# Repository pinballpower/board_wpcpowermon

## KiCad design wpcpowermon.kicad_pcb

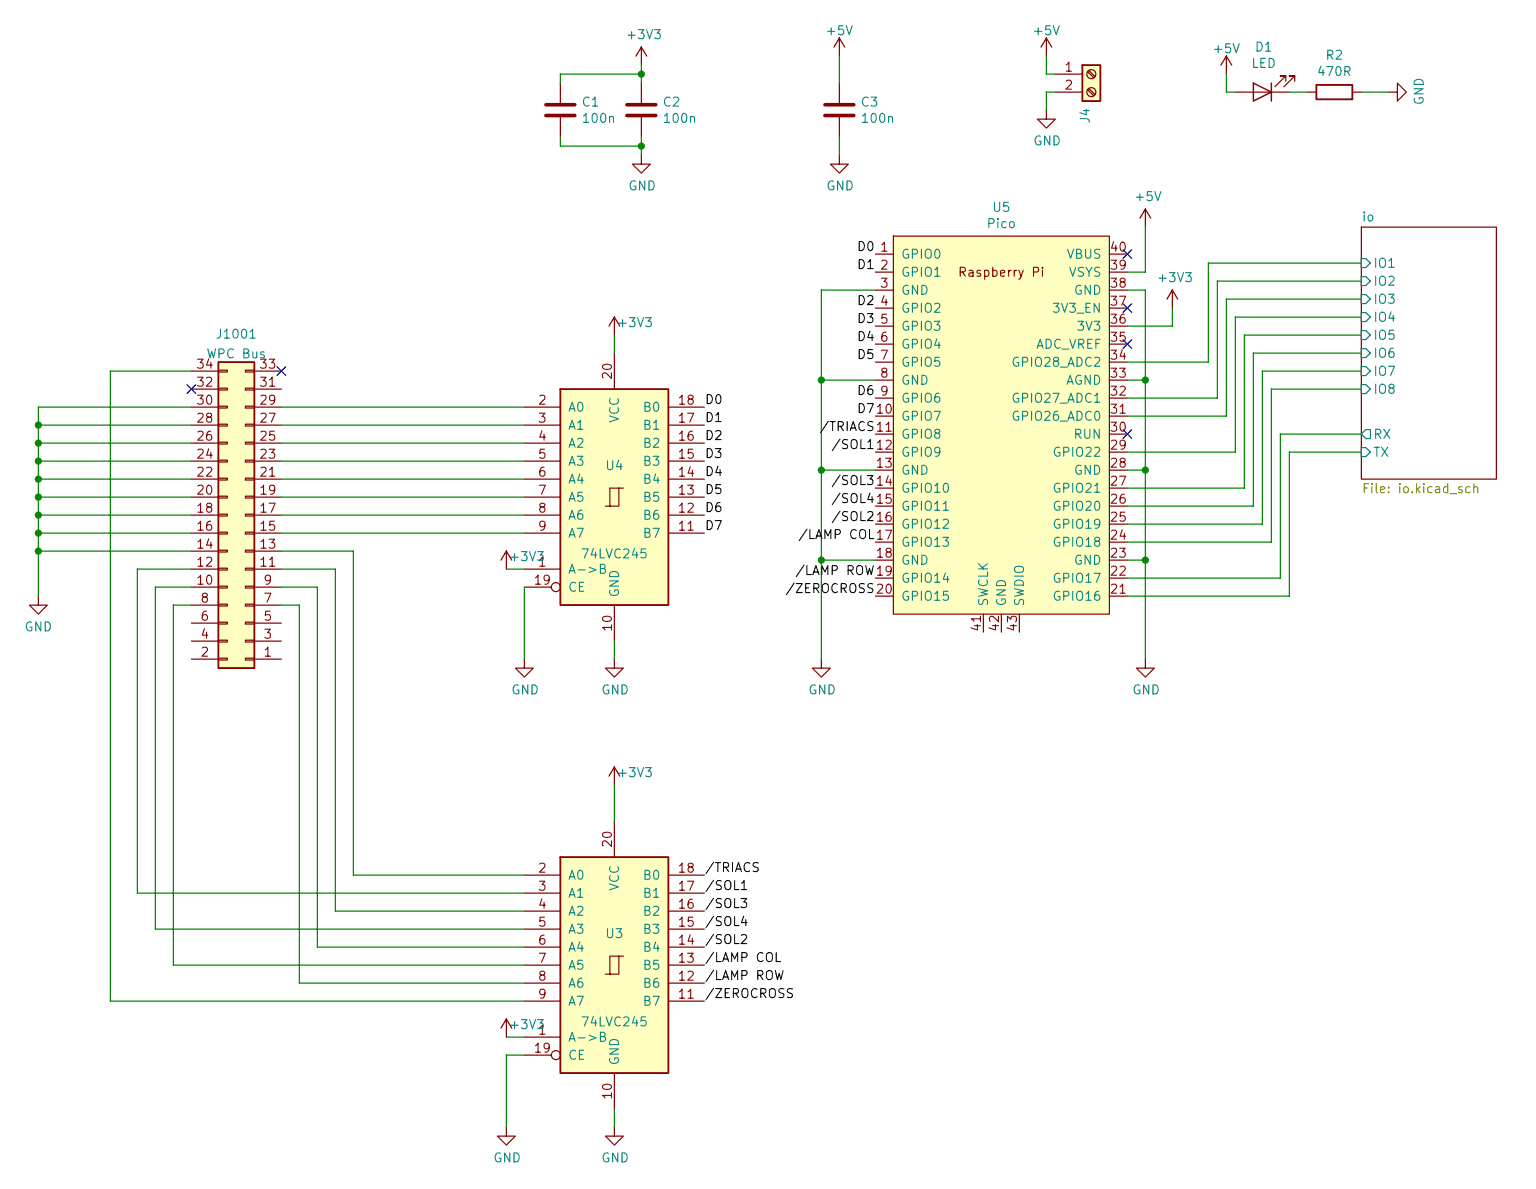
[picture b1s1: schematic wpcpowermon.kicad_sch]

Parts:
C1, C2, C3: 100n; C_Disc_D3.0mm_W2.0mm_P2.50mm
D1: LED; LED_D1.8mm_W3.3mm_H2.4mm
J4: 5V; TerminalBlock_4Ucon_1x02_P3.50mm_Horizontal
J1001: WPC Bus; PinHeader_2x17_P2.54mm_Vertical
R2: 470R; R_Axial_DIN0204_L3.6mm_D1.6mm_P5.08mm_Horizontal
U3, U4: 74LVC245; DIP-20_W7.62mm_LongPads
U5: Pico; RPi_Pico_SMD_TH

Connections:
+3V3: C1.1, C2.1, U3.1 (A->B), U3.20 (VCC), U4.1 (A->B), U4.20 (VCC), U5.36 (3V3)
+5V: C3.1, D1.2 (A), J4.1, U5.39 (VSYS); also elsewhere on the board
/D0: U4.18 (B0), U5.1 (GPIO0)
/D1: U4.17 (B1), U5.2 (GPIO1)
/D2: U4.16 (B2), U5.4 (GPIO2)
/D3: U4.15 (B3), U5.5 (GPIO3)
/D4: U4.14 (B4), U5.6 (GPIO4)
/D5: U4.13 (B5), U5.7 (GPIO5)
/D6: U4.12 (B6), U5.9 (GPIO6)
/D7: U4.11 (B7), U5.10 (GPIO7)
/io/IO1: U5.34 (GPIO28_ADC2); also elsewhere on the board
/io/IO2: U5.32 (GPIO27_ADC1); also elsewhere on the board
/io/IO3: U5.31 (GPIO26_ADC0); also elsewhere on the board
/io/IO4: U5.29 (GPIO22); also elsewhere on the board
/io/IO5: U5.27 (GPIO21); also elsewhere on the board
/io/IO6: U5.26 (GPIO20); also elsewhere on the board
/io/IO7: U5.25 (GPIO19); also elsewhere on the board
/io/IO8: U5.24 (GPIO18); also elsewhere on the board
/io/RX: U5.22 (GPIO17); also elsewhere on the board
/io/TX: U5.21 (GPIO16); also elsewhere on the board
//LAMP COL: U3.13 (B5), U5.17 (GPIO13)
//LAMP ROW: U3.12 (B6), U5.19 (GPIO14)
//SOL1: U3.17 (B1), U5.12 (GPIO9)
//SOL2: U3.14 (B4), U5.16 (GPIO12)
//SOL3: U3.16 (B2), U5.14 (GPIO10)
//SOL4: U3.15 (B3), U5.15 (GPIO11)
//TRIACS: U3.18 (B0), U5.11 (GPIO8)
//ZEROCROSS: U3.11 (B7), U5.20 (GPIO15)
GND: C1.2, C2.2, C3.2, J4.2, J1001.14, J1001.16, J1001.18, J1001.20, J1001.22, J1001.24, J1001.26, J1001.28, J1001.30, R2.2, U3.10 (GND), U3.19 (CE), U4.10 (GND), U4.19 (CE), U5.3 (GND), U5.8 (GND), U5.13 (GND), U5.18 (GND), U5.23 (GND), U5.28 (GND), U5.33 (AGND), U5.38 (GND); also elsewhere on the board
unnamed: D1.1 (K), R2.1
unnamed: J1001.7, U3.8 (A6)
unnamed: J1001.8, U3.7 (A5)
unnamed: J1001.9, U3.6 (A4)
unnamed: J1001.10, U3.5 (A3)
unnamed: J1001.11, U3.4 (A2)
unnamed: J1001.12, U3.3 (A1)
unnamed: J1001.13, U3.2 (A0)
unnamed: J1001.15, U4.9 (A7)
unnamed: J1001.17, U4.8 (A6)
unnamed: J1001.19, U4.7 (A5)
unnamed: J1001.21, U4.6 (A4)
unnamed: J1001.23, U4.5 (A3)
unnamed: J1001.25, U4.4 (A2)
unnamed: J1001.27, U4.3 (A1)
unnamed: J1001.29, U4.2 (A0)
unnamed: J1001.34, U3.9 (A7)

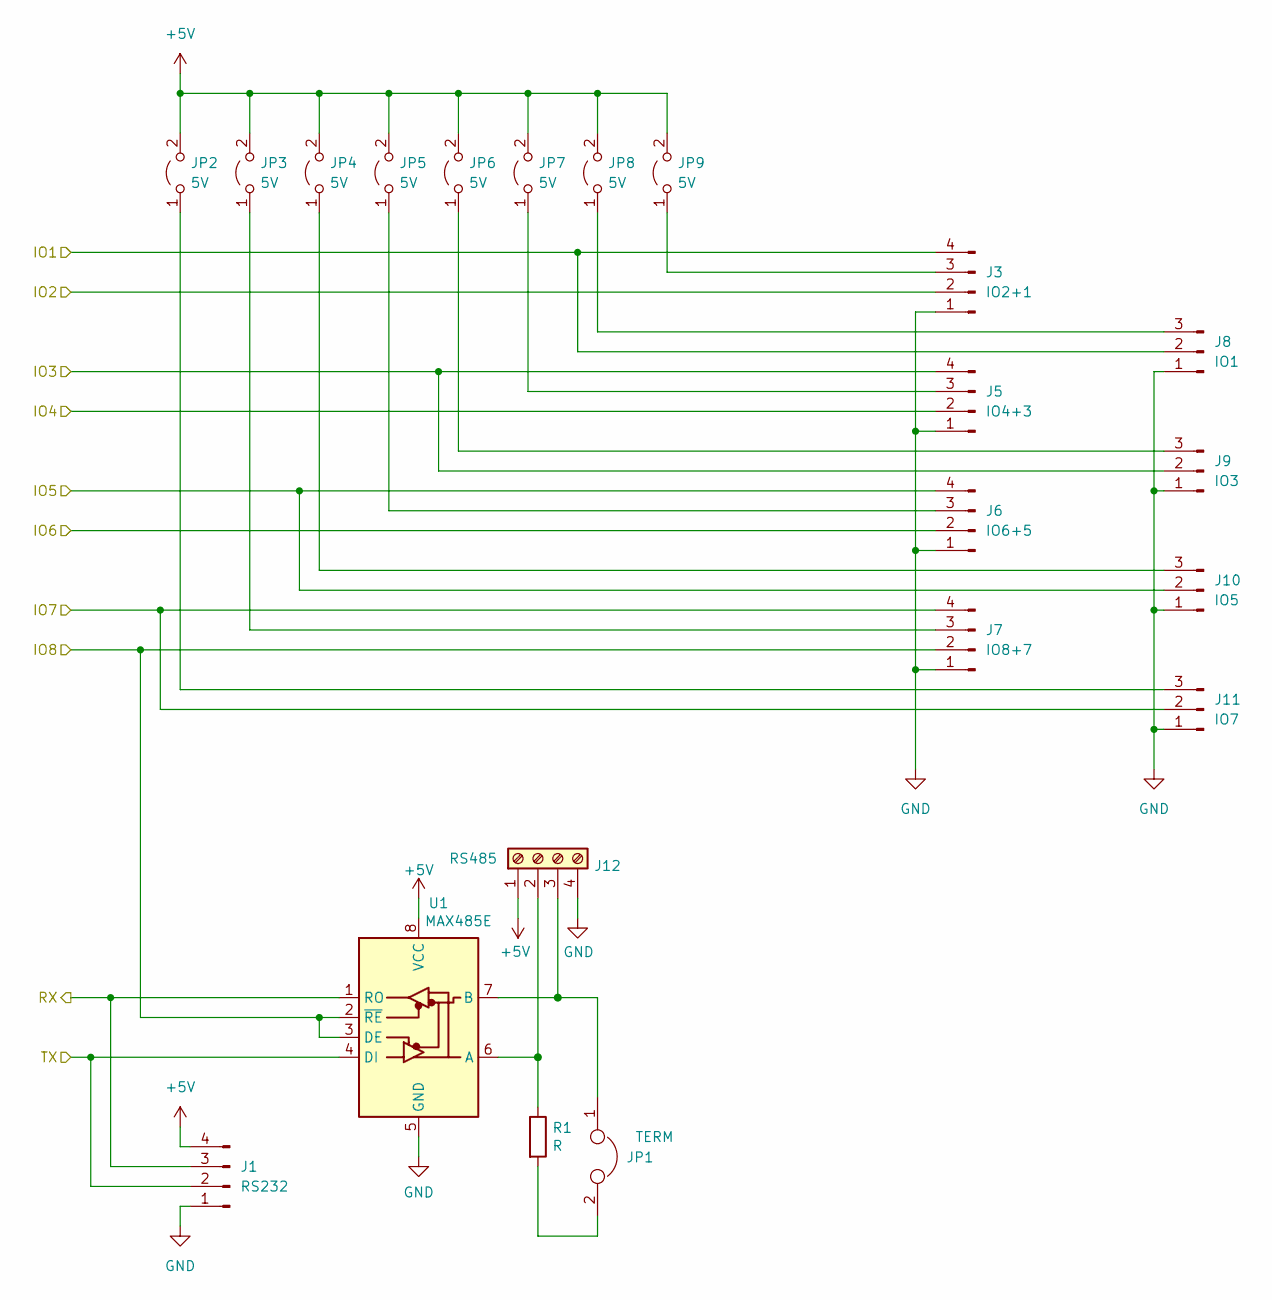
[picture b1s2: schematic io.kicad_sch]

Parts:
J1: RS232; Molex_KK-254_AE-6410-04A_1x04_P2.54mm_Vertical
J3: IO2+1; Molex_KK-254_AE-6410-04A_1x04_P2.54mm_Vertical
J5: IO4+3; Molex_KK-254_AE-6410-04A_1x04_P2.54mm_Vertical
J6: IO6+5; Molex_KK-254_AE-6410-04A_1x04_P2.54mm_Vertical
J7: IO8+7; Molex_KK-254_AE-6410-04A_1x04_P2.54mm_Vertical
J8: IO1; Molex_KK-254_AE-6410-03A_1x03_P2.54mm_Vertical
J9: IO3; Molex_KK-254_AE-6410-03A_1x03_P2.54mm_Vertical
J10: IO5; Molex_KK-254_AE-6410-03A_1x03_P2.54mm_Vertical
J11: IO7; Molex_KK-254_AE-6410-03A_1x03_P2.54mm_Vertical
J12: RS485; TerminalBlock_4Ucon_1x04_P3.50mm_Horizontal
JP1: TERM; PinHeader_1x02_P2.54mm_Vertical
JP2, JP3, JP4, JP5, JP6, JP7, JP8, JP9: 5V; PinHeader_1x02_P2.54mm_Vertical
R1: R; R_Axial_DIN0204_L3.6mm_D1.6mm_P5.08mm_Horizontal
U1: MAX485E; DIP-8_W7.62mm_LongPads

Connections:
+5V: J1.4, J12.1, JP2.2 (B), JP3.2 (B), JP4.2 (B), JP5.2 (B), JP6.2 (B), JP7.2 (B), JP8.2 (B), JP9.2 (B), U1.8 (VCC); also elsewhere on the board
/io/IO1: J3.4, J8.2; also elsewhere on the board
/io/IO2: J3.2; also elsewhere on the board
/io/IO3: J5.4, J9.2; also elsewhere on the board
/io/IO4: J5.2; also elsewhere on the board
/io/IO5: J6.4, J10.2; also elsewhere on the board
/io/IO6: J6.2; also elsewhere on the board
/io/IO7: J7.4, J11.2; also elsewhere on the board
/io/IO8: J7.2, U1.2 (~RE), U1.3 (DE); also elsewhere on the board
/io/RX: J1.3, U1.1 (RO); also elsewhere on the board
/io/TX: J1.2, U1.4 (DI); also elsewhere on the board
GND: J1.1, J3.1, J5.1, J6.1, J7.1, J8.1, J9.1, J10.1, J11.1, J12.4, U1.5 (GND); also elsewhere on the board
unnamed: J3.3, JP9.1 (A)
unnamed: J5.3, JP7.1 (A)
unnamed: J6.3, JP5.1 (A)
unnamed: J7.3, JP3.1 (A)
unnamed: J8.3, JP8.1 (A)
unnamed: J9.3, JP6.1 (A)
unnamed: J10.3, JP4.1 (A)
unnamed: J11.3, JP2.1 (A)
unnamed: J12.2, R1.1, U1.6 (A)
unnamed: J12.3, JP1.1, U1.7 (B)
unnamed: JP1.2, R1.2

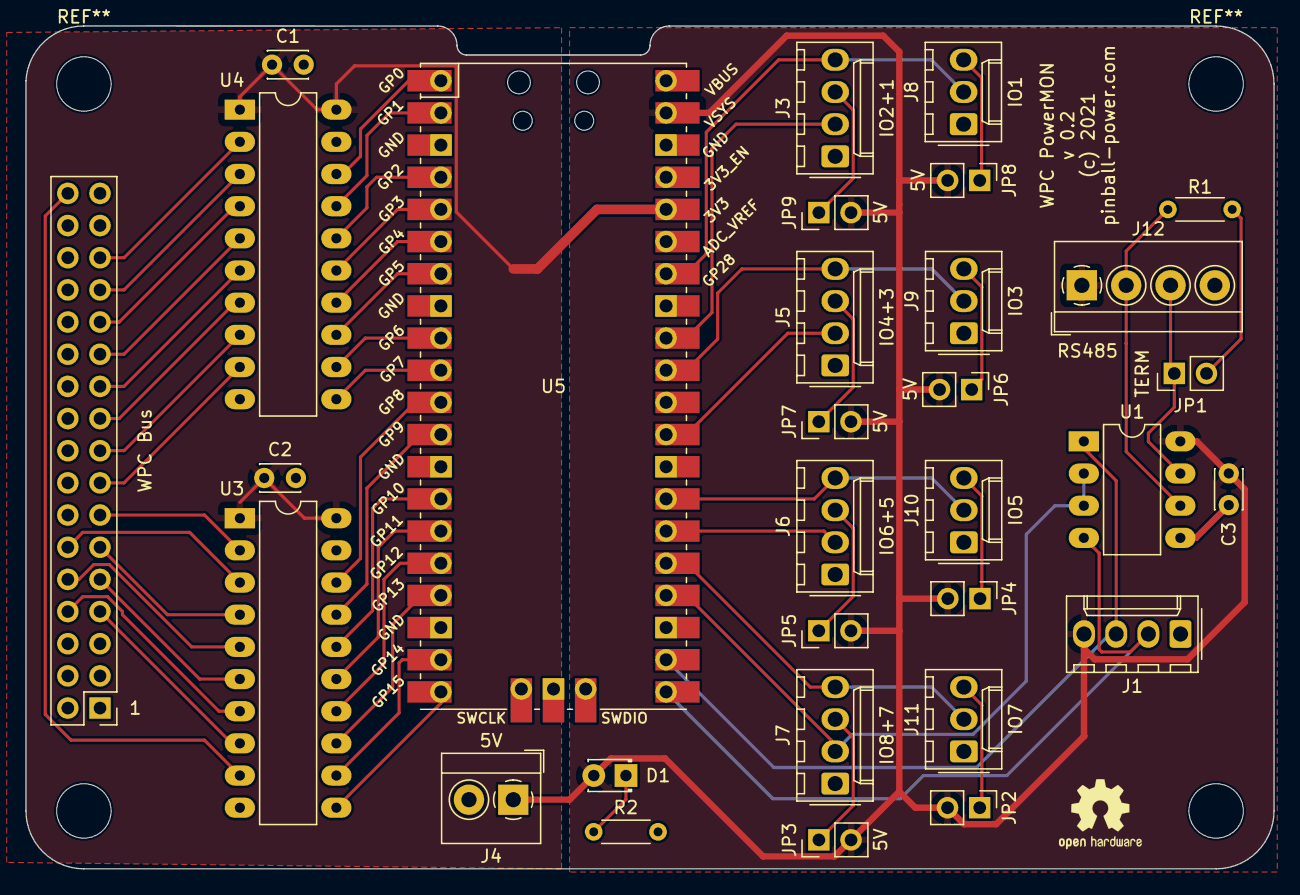
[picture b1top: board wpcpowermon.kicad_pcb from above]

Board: 2 copper layers, 98.6 x 66.6 mm, 31 parts (0 on the bottom side), 57 nets.

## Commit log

2021-09-14 Initial checkin
2021-09-14 First PCB draft
2021-11-07 Version 0.1
2022-01-30 Gerber 0.2 released
2022-01-30 v 0.2
2022-01-30 Added OHC logo

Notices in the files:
wpcpowermon.kicad_pcb:
(c) 2021
